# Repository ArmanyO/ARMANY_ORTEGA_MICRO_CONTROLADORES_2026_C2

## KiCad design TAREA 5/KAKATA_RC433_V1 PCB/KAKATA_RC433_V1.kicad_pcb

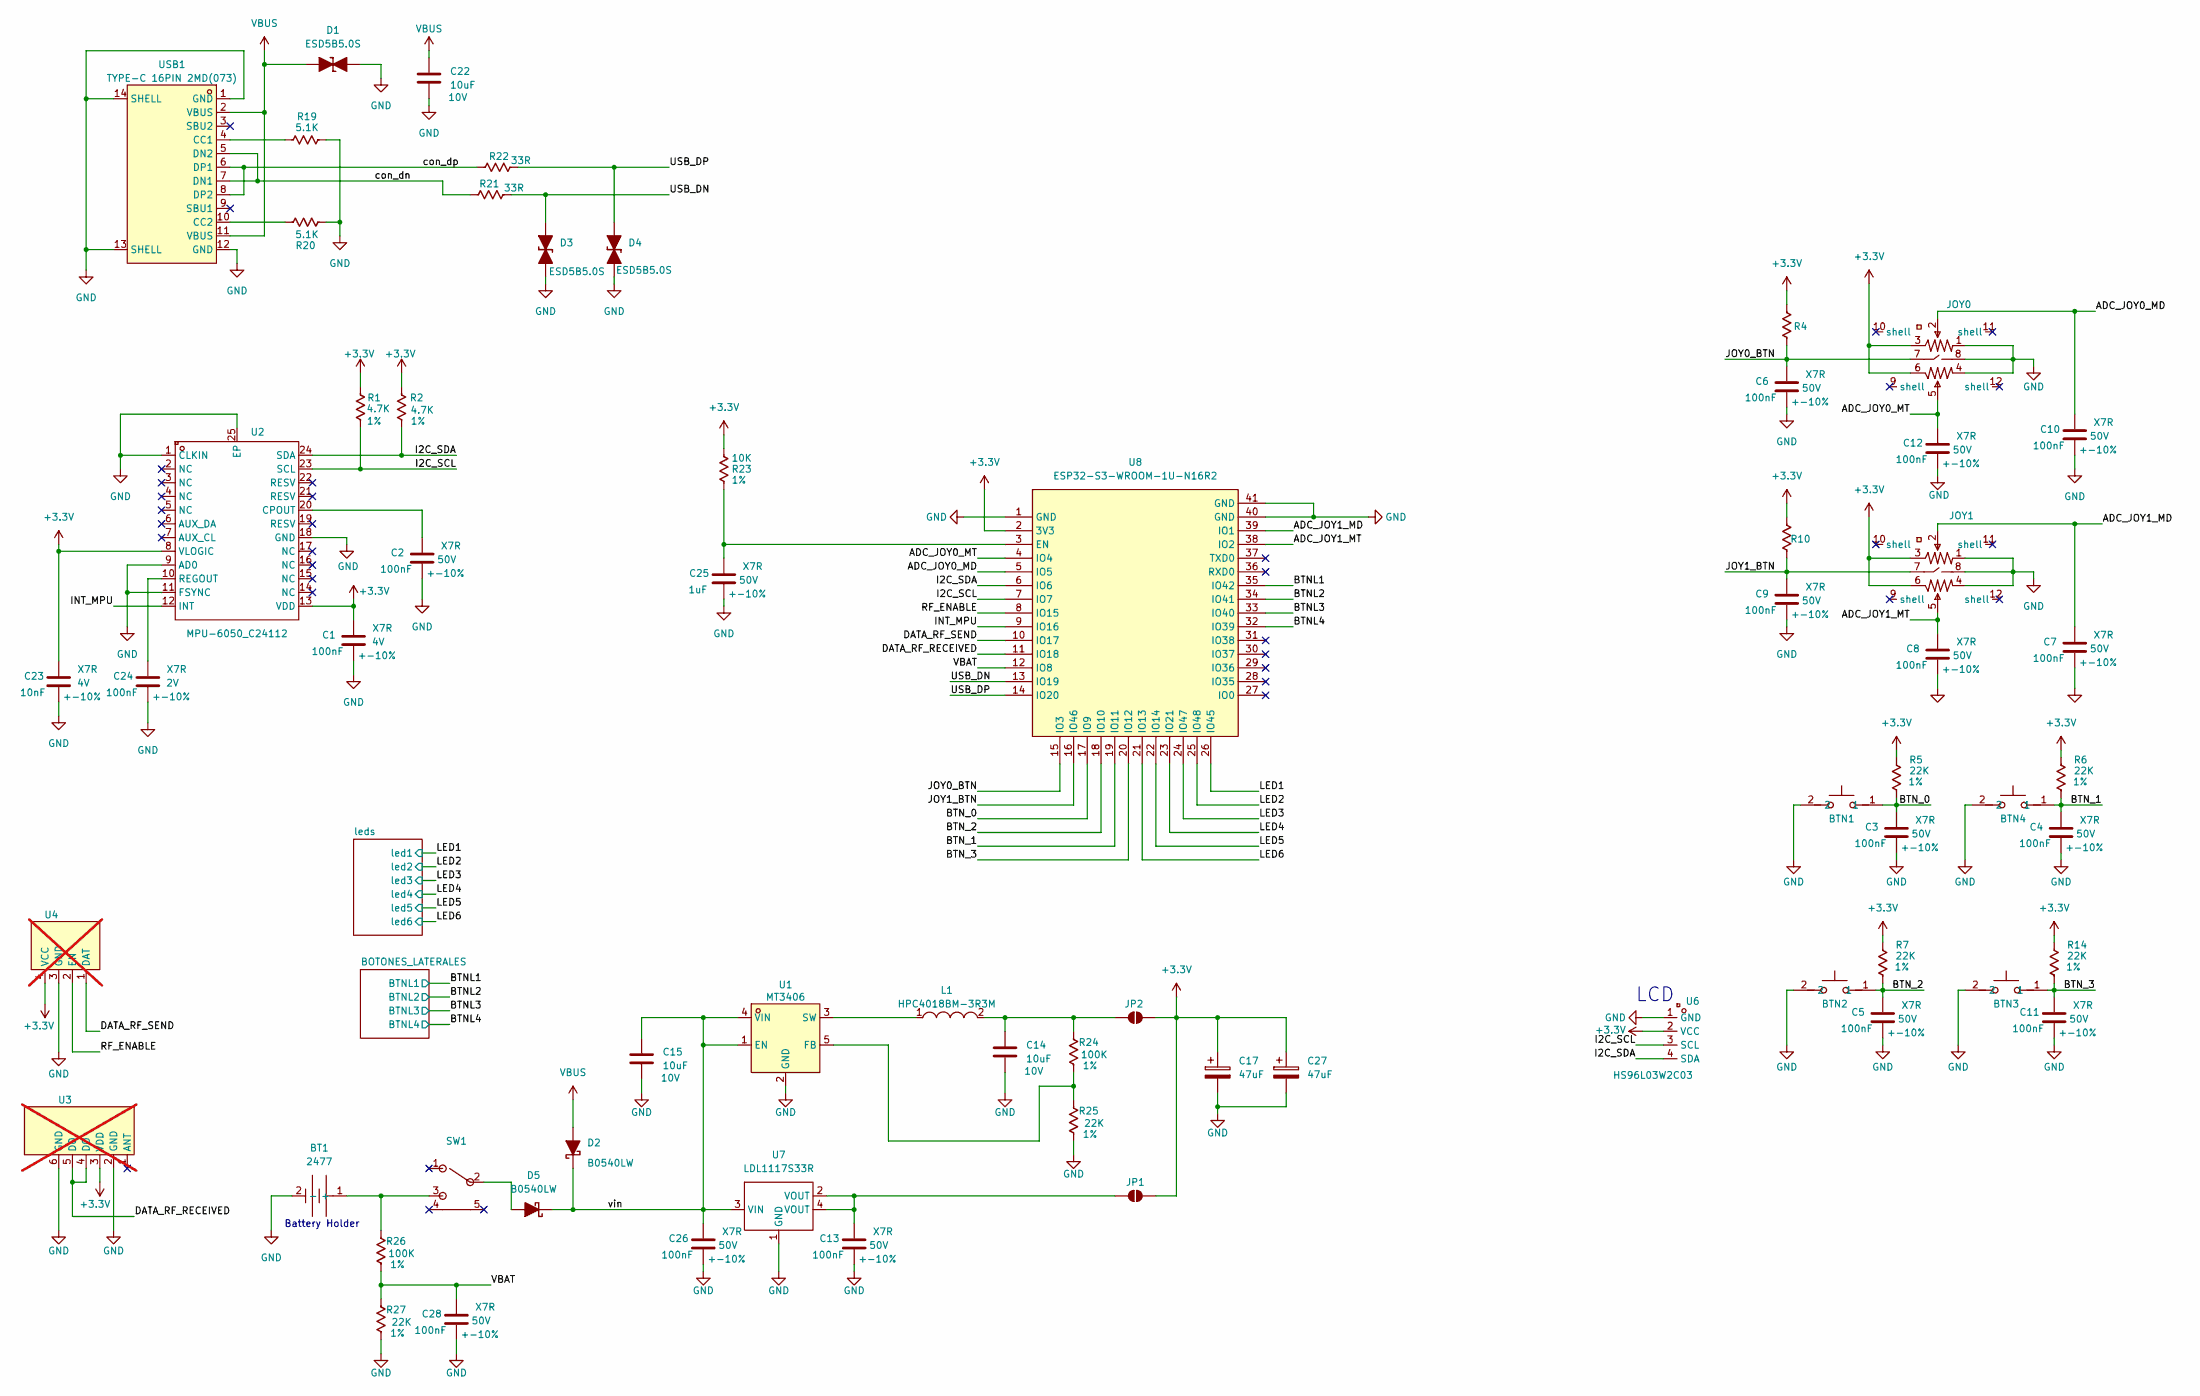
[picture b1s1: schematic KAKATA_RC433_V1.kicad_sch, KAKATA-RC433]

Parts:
BT1: 2477; BAT-TH_2477; LCSC Part C238090
BTN1, BTN2, BTN3, BTN4: CPG151101D01; SW-TH_CPG151101D9X; LCSC Part C49234238
C1, C24: 100nF; C_0603_1608Metric; LCSC Part C519438
C2, C3, C4, C5, C6, C7, C8, C9, C10, C11, C12, C13, C26, C28: 100nF; C_0603_1608Metric; LCSC Part C14663
C14, C15, C22: 10uF; C_0805_2012Metric; LCSC Part # C15850
C17, C27: 47uF; CP_Elec_6.3x5.2; LCSC Part C72522
C23: 10nF; C_0603_1608Metric; LCSC Part C100042
C25: 1uF; C_0603_1608Metric; LCSC Part C559769
D1, D3, D4: ESD5B5.0S; D_SOD-523; LCSC Part # C5172939
D2, D5: B0540LW; D_SOD-123; LCSC Part # C8570
JOY0, JOY1: YF16S-FL7.2-B5KB(45-10)-Y; JOYTICK-TH_YF16S-FL7.2-B5KB-45-10-Y_1; LCSC Part C37323740
JP1, JP2: SolderJumper_2_Open; SolderJumper-2_P1.3mm_Open_RoundedPad1.0x1.5mm
L1: HPC4018BM-3R3M; IND-SMD_L4.0-W4.0_HPC4030NF; PART_NUMBER HPC4018BM-3R3M; LCSC Part C692161
R1, R2: 4.7K; R_0603_1608Metric; LCSC Part C99782
R4, R5, R6, R7, R10, R14, R25, R27: 22K; R_0603_1608Metric; LCSC Part C114065
R19, R20: 5.1K; R_0603_1608Metric; LCSC Part # C105580
R21, R22: 33R; R_0603_1608Metric; LCSC Part # C108661
R23: 10K; R_0603_1608Metric; LCSC Part C98220
R24, R26: 100K; R_0603_1608Metric; LCSC Part C14675
SW1: ST-0-102-C03-N003-RS; SW-TH_ST-0-102-C03-N003-RS; LCSC Part C1788489
U1: MT3406; SOT-23-5_L2.9-W1.6-P0.95-LS2.8-BR; LCSC Part C22462728
U2: MPU-6050_C24112; QFN-24_L4.0-W4.0-P0.50-BL-EP2.7; LCSC Part C24112
U3: 433 MHz RF RECEIVER; rf_433mhz_receiver; not fitted
U4: 433 MHz TRANSMITTER; RF_433MHz_transmisor; not fitted
U6: HS96L03W2C03; OLED-TH_L27.8-W27.2-P2.54_C9900033791; LCSC Part C5248080
U7: LDL1117S33R; SOT-223-4_L6.5-W3.5-P2.30-LS7.0-BR; LCSC Part C435835
U8: ESP32-S3-WROOM-1U-N16R2; WIRELM-SMD_ESP32-S3-WROOM-1U; LCSC Part C3013945
USB1: TYPE-C 16PIN 2MD(073); USB-C-SMD_TYPE-C-6PIN-2MD-073; LCSC Part C2765186

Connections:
+3.3V: C1.1, C17.1, C23.1, C27.1, JOY0.3, JOY0.6, JOY1.3, JOY1.6, JP1.2 (B), JP2.2 (B), R1.1, R2.1, R4.1, R5.2, R6.2, R7.2, R10.1, R14.2, R23.1, U2.8 (VLOGIC), U2.13 (VDD), U3.3 (VDD), U4.4 (VCC), U6.2 (VCC), U8.2 (3V3); also elsewhere on the board
/ADC_JOY0_MD: C10.1, JOY0.2, U8.5 (IO5)
/ADC_JOY0_MT: C12.1, JOY0.5, U8.4 (IO4)
/ADC_JOY1_MD: C7.1, JOY1.2, U8.39 (IO1)
/ADC_JOY1_MT: C8.1, JOY1.5, U8.38 (IO2)
/BTNL1: U8.35 (IO42); also elsewhere on the board
/BTNL2: U8.34 (IO41); also elsewhere on the board
/BTNL3: U8.33 (IO40); also elsewhere on the board
/BTNL4: U8.32 (IO39); also elsewhere on the board
/BTN_0: BTN1.1, C3.1, R5.1, U8.17 (IO9)
/BTN_1: BTN4.1, C4.1, R6.1, U8.19 (IO11)
/BTN_2: BTN2.1, C5.1, R7.1, U8.18 (IO10)
/BTN_3: BTN3.1, C11.1, R14.1, U8.20 (IO12)
/DATA_RF_RECEIVED: U3.4 (DO), U3.5 (DO), U8.11 (IO18)
/DATA_RF_SEND: U4.1 (DAT), U8.10 (IO17)
/I2C_SCL: R1.2, U2.23 (SCL), U6.3 (SCL), U8.7 (IO7)
/I2C_SDA: R2.2, U2.24 (SDA), U6.4 (SDA), U8.6 (IO6)
/INT_MPU: U2.12 (INT), U8.9 (IO16)
/JOY0_BTN: C6.1, JOY0.7, R4.2, U8.15 (IO3)
/JOY1_BTN: C9.1, JOY1.7, R10.2, U8.16 (IO46)
/LED1: U8.26 (IO45); also elsewhere on the board
/LED2: U8.25 (IO48); also elsewhere on the board
/LED3: U8.24 (IO47); also elsewhere on the board
/LED4: U8.23 (IO21); also elsewhere on the board
/LED5: U8.22 (IO14); also elsewhere on the board
/LED6: U8.21 (IO13); also elsewhere on the board
/RF_ENABLE: U4.2 (EN), U8.8 (IO15)
/USB_DN: D3.2 (A), R21.2, U8.13 (IO19)
/USB_DP: D4.2 (A), R22.2, U8.14 (IO20)
/VBAT: C28.1, R26.2, R27.1, U8.12 (IO8)
/con_dn: R21.1, USB1.5 (DN2), USB1.7 (DN1)
/con_dp: R22.1, USB1.6 (DP1), USB1.8 (DP2)
/vin: C15.1, C26.1, D2.1 (K), D5.1 (K), U1.1 (EN), U1.4 (VIN), U7.3 (VIN)
GND: BT1.2 (-), BTN1.2, BTN2.2, BTN3.2, BTN4.2, C1.2, C2.2, C3.2, C4.2, C5.2, C6.2, C7.2, C8.2, C9.2, C10.2, C11.2, C12.2, C13.2, C14.2, C15.2, C17.2, C22.2, C23.2, C24.2, C25.2, C26.2, C27.2, C28.2, D1.1 (K), D3.1 (K), D4.1 (K), JOY0.1, JOY0.4, JOY0.8, JOY1.1, JOY1.4, JOY1.8, R19.2, R20.2, R25.2, R27.2, U1.2 (GND), U2.1 (CLKIN), U2.9 (AD0), U2.11 (FSYNC), U2.18 (GND), U2.25 (EP), U3.2 (GND), U3.6 (GND), U4.3 (GND), U6.1 (GND), U7.1 (GND), U8.1 (GND), U8.40 (GND), U8.41 (GND), USB1.1 (GND), USB1.12 (GND), USB1.13 (SHELL), USB1.14 (SHELL); also elsewhere on the board
unnamed: BT1.1 (+), R26.1, SW1.3
unnamed: D5.2 (A), SW1.2
unnamed: C13.1, JP1.1 (A), U7.2 (VOUT), U7.4 (VOUT)
unnamed: C14.1, JP2.1 (A), L1.2, R24.1
unnamed: R24.2, R25.1, U1.5 (FB)
unnamed: L1.1, U1.3 (SW)
unnamed: C2.1, U2.20 (CPOUT)
unnamed: C24.1, U2.10 (REGOUT)
unnamed: C25.1, R23.2, U8.3 (EN)
unnamed: R19.1, USB1.4 (CC1)
unnamed: R20.1, USB1.10 (CC2)
VBUS: C22.1, D1.2 (A), D2.2 (A), USB1.2 (VBUS), USB1.11 (VBUS)

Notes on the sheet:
Battery Holder
LCD

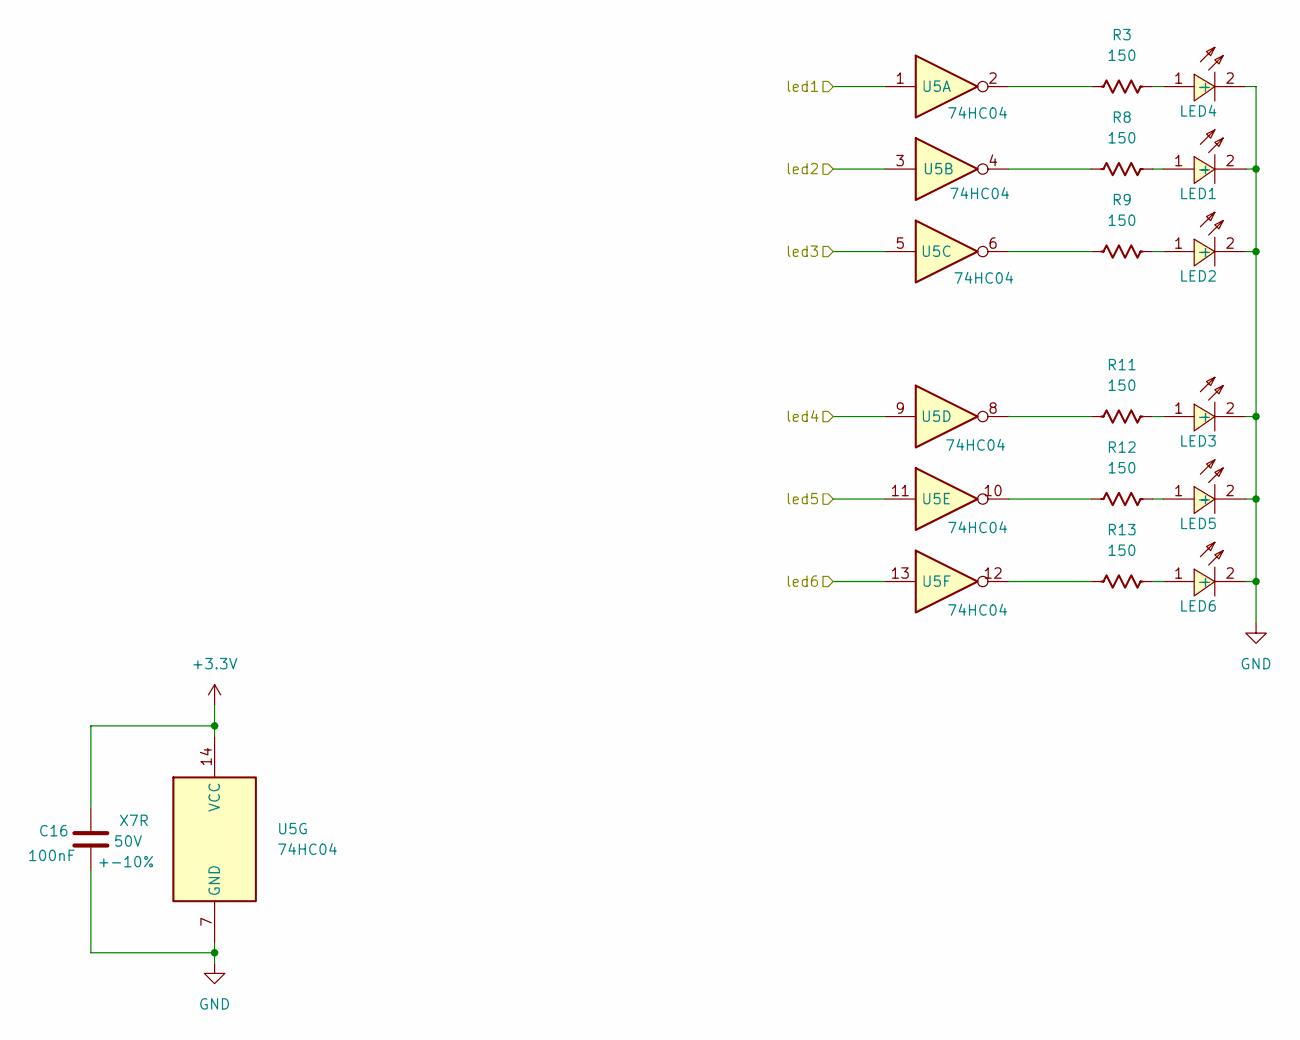
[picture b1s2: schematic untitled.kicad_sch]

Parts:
C16: 100nF; C_0603_1608Metric; LCSC Part C14663
LED1, LED2, LED3, LED4, LED5, LED6: YLED0603R; LED_0603_1608Metric; LCSC Part C19171390
R3, R8, R9, R11, R12, R13: 150; R_0603_1608Metric; LCSC Part C107696
U5: 74HC04; SOIC-14_3.9x8.65mm_Pitch1.27mm; LCSC Part C5590

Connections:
+3.3V: C16.1, U5.14 (VCC); also elsewhere on the board
/LED1: U5.1; also elsewhere on the board
/LED2: U5.3; also elsewhere on the board
/LED3: U5.5; also elsewhere on the board
/LED4: U5.9; also elsewhere on the board
/LED5: U5.11; also elsewhere on the board
/LED6: U5.13; also elsewhere on the board
GND: C16.2, LED1.2 (-), LED2.2 (-), LED3.2 (-), LED4.2 (-), LED5.2 (-), LED6.2 (-), U5.7 (GND); also elsewhere on the board
unnamed: LED1.1 (+), R8.2
unnamed: LED2.1 (+), R9.2
unnamed: LED3.1 (+), R11.2
unnamed: LED4.1 (+), R3.2
unnamed: LED5.1 (+), R12.2
unnamed: LED6.1 (+), R13.2
unnamed: R3.1, U5.2
unnamed: R8.1, U5.4
unnamed: R9.1, U5.6
unnamed: R11.1, U5.8
unnamed: R12.1, U5.10
unnamed: R13.1, U5.12

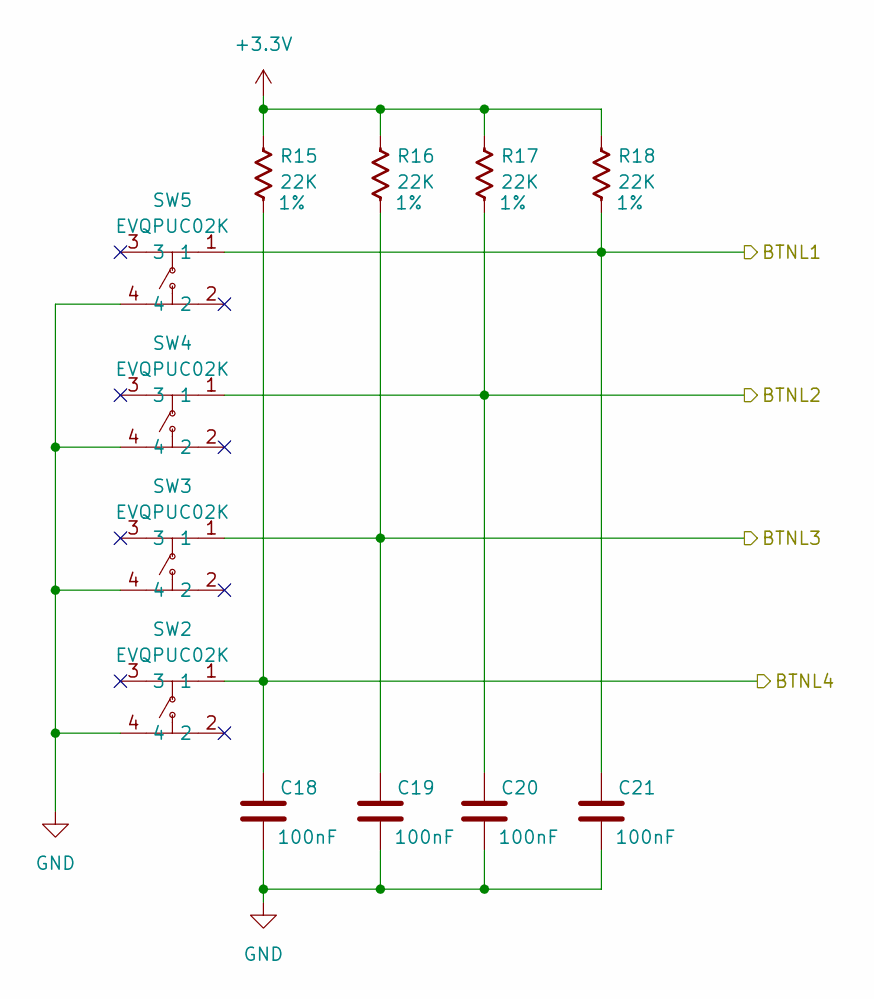
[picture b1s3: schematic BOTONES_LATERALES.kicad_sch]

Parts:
C18, C19, C20, C21: 100nF; C_0603_1608Metric; LCSC Part C14663
R15, R16, R17, R18: 22K; R_0603_1608Metric; LCSC Part C114065
SW2, SW3, SW4, SW5: EVQPUC02K; SW-SMD_EVQPUD02K; LCSC Part C79174

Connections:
+3.3V: R15.1, R16.1, R17.1, R18.1; also elsewhere on the board
/BTNL1: C21.1, R18.2, SW5.1; also elsewhere on the board
/BTNL2: C20.1, R17.2, SW4.1; also elsewhere on the board
/BTNL3: C19.1, R16.2, SW3.1; also elsewhere on the board
/BTNL4: C18.1, R15.2, SW2.1; also elsewhere on the board
GND: C18.2, C19.2, C20.2, C21.2, SW2.4, SW3.4, SW4.4, SW5.4; also elsewhere on the board

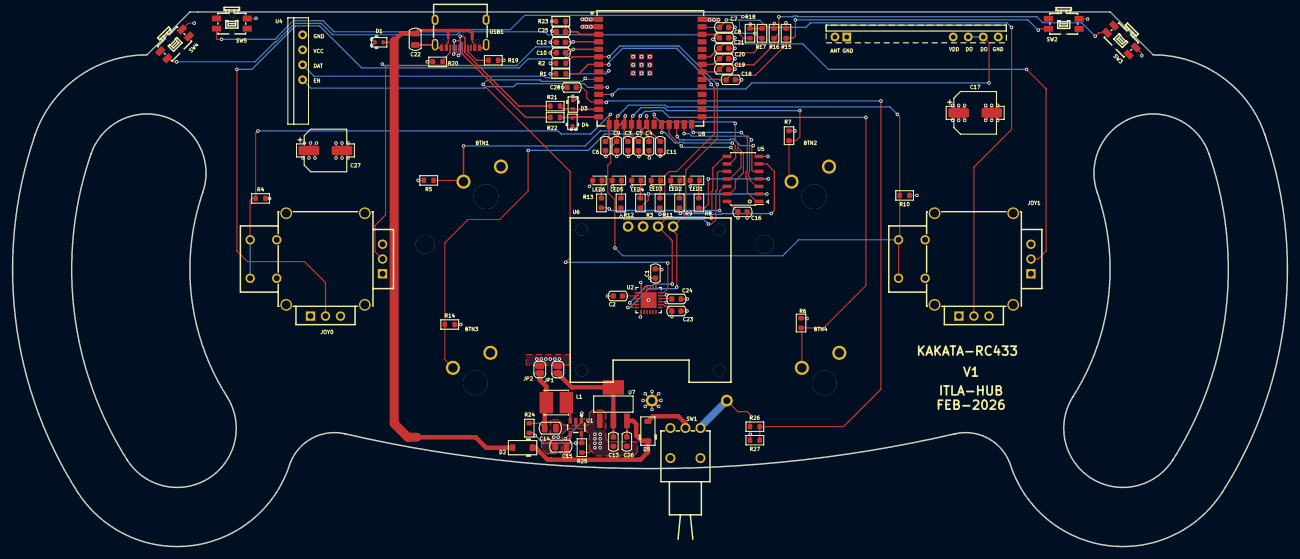
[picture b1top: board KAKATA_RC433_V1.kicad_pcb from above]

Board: 4 copper layers, 215.7 x 90.3 mm, 90 parts (1 on the bottom side), 58 nets.

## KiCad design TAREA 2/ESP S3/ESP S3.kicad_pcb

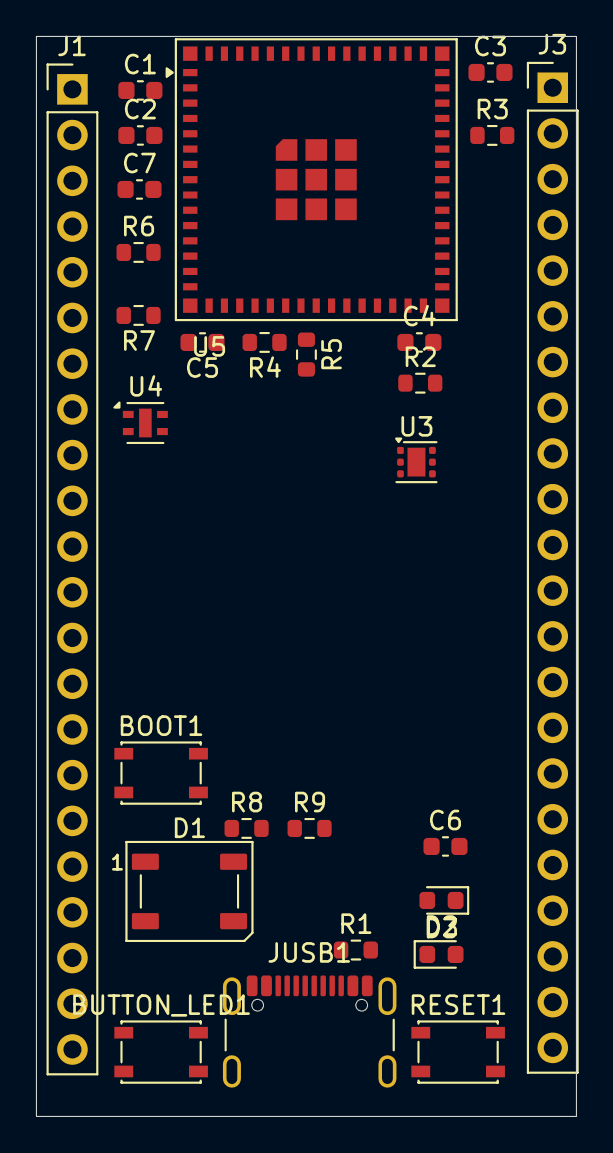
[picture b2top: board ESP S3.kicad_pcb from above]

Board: 2 copper layers, 30.0 x 60.0 mm, 28 parts (0 on the bottom side), 48 nets, no tracks yet.

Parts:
BOOT1: SW_SPST_PTS810
BUTTON_LED1: SW_SPST_PTS810
C1, C3, C4, C5: 0.1uF; C_0603_1608Metric
C2, C6, C7: 10uF; C_0603_1608Metric
D1: WS2812B; LED_WS2812B_PLCC4_5.0x5.0mm_P3.2mm
D2, D3: LED; LED_0603_1608Metric
J1, J3: PinHeader_1x22_P2.54mm_Vertical
JUSB1: USB_C_Receptacle_USB2.0; USB_C_Receptacle_GCT_USB4105-xx-A_16P_TopMnt_Horizontal
R1, R2, R8, R9: 5.1k; R_0603_1608Metric
R3, R4, R5: 10k; R_0603_1608Metric
R6: 1M; R_0603_1608Metric
R7: 200k; R_0603_1608Metric
RESET1: SW_SPST_PTS810
U3: TLV75801PDRV; WSON-6-1EP_2x2mm_P0.65mm_EP1x1.6mm
U4: ENS210; AMS_QFN-4-1EP_2x2mm_P0.95mm_EP0.7x1.6mm
U5: ESP32-S3-MINI-1U; ESP32-S2-MINI-1U

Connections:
/3V3: C1.1, C2.1, C5.1, C7.1, D1.1 (VDD), J1.1, R3.2, R4.2, R5.2, R6.2, R8.1, U3.1 (OUT), U4.1 (VDD), U5.3 (3V3)
/5VUSB: C6.1, J1.21, JUSB1.A4 (VBUS), JUSB1.A9 (VBUS), JUSB1.B4 (VBUS), JUSB1.B9 (VBUS), U3.4 (EN), U3.6 (IN)
/ESP32_EN: C3.1, J3.2, R3.1, U5.45 (EN)
/GPIO0: C4.1, J1.2, U5.4 (IO0)
/GPIO1: J1.3, U5.5 (IO1)
/GPIO2: J1.4, U5.6 (IO2)
/GPIO3: J1.5, U5.7 (IO3)
/GPIO4: J1.6, U5.8 (IO4)
/GPIO5: J1.7, U5.9 (IO5)
/GPIO6: J1.8, U5.10 (IO6)
/GPIO7: J1.9, U5.11 (IO7)
/GPIO8: J1.10, U5.12 (IO8)
/GPIO9: J1.11, U5.13 (IO9)
/GPIO10: J1.12, U5.14 (IO10)
/GPIO11: J1.13, U5.15 (IO11)
/GPIO12: J1.14, U5.16 (IO12)
/GPIO13: J1.15, U5.17 (IO13)
/GPIO14: J1.16, U5.18 (IO14)
/GPIO15: J1.17, U5.19 (IO15)
/GPIO16: J1.18, U5.20 (IO16)
/GPIO21: J3.18, U5.25 (IO21)
/GPIO26: J3.17, U5.26 (IO26)
/GPIO33: J3.16, U5.28 (IO33)
/GPIO34: J3.15, U5.29 (IO34)
/GPIO35: J3.14, U5.31 (IO35)
/GPIO36: J3.13, U5.32 (IO36)
/GPIO37: J3.12, U5.33 (IO37)
/GPIO38: J3.11, U5.34 (IO38)
/GPIO39: J3.10, U5.35 (IO39)
/GPIO40: J3.9, U5.36 (IO40)
/GPIO41: J3.8, U5.37 (IO41)
/GPIO42: J3.7, U5.38 (IO42)
/GPIO45: J3.4, U5.41 (IO45)
/GPIO46: J3.3, U5.44 (IO46)
/GPIO47: J3.22, U5.27 (IO47)
/GPIO48: D1.4 (DIN), J3.21, U5.30 (IO48)
/I2C_SCL: J1.19, R4.1, U4.2 (SCL), U5.21 (IO17)
/I2C_SDA: J1.20, R5.1, U4.3 (SDA), U5.22 (IO18)
/RXD: J3.5, U5.40 (RXD0)
/TXD: J3.6, U5.39 (TXD0)
/USB_N: JUSB1.A7 (D-), JUSB1.B7 (D-), U5.23 (USB_D-)
/USB_P: JUSB1.A6 (D+), JUSB1.B6 (D+), U5.24 (USB_D+)
GND: BOOT1.1, BOOT1.2, C1.2, C2.2, C3.2, C4.2, C5.2, C6.2, C7.2, D1.3 (VSS), D2.1 (K), D3.1 (K), J1.22, J3.1, JUSB1.A1 (GND), JUSB1.A12 (GND), JUSB1.B1 (GND), JUSB1.B12 (GND), R1.2, R2.2, R7.1, RESET1.1, RESET1.2, U3.3 (GND), U3.7 (GND), U4.4 (GND), U4.5 (GND), U5.1 (GND), U5.2 (GND), U5.42 (GND), U5.43 (GND), U5.46 (GND), U5.47 (GND), U5.48 (GND), U5.49 (GND), U5.50 (GND), U5.51 (GND), U5.52 (GND), U5.53 (GND), U5.54 (GND), U5.55 (GND), U5.56 (GND), U5.57 (GND), U5.58 (GND), U5.59 (GND), U5.60 (GND), U5.61 (GND), U5.62 (GND), U5.63 (GND), U5.64 (GND), U5.65 (GND)
unnamed: BUTTON_LED1.1, BUTTON_LED1.2, R9.2
unnamed: D2.2 (A), R8.2, R9.1
unnamed: JUSB1.A5 (CC1), R2.1
unnamed: JUSB1.B5 (CC2), R1.1
unnamed: R6.1, R7.2, U3.2 (FB)

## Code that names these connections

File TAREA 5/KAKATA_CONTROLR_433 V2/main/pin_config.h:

#ifndef PIN_CONFIG_H
#define PIN_CONFIG_H

// ============================================================
// KAKATA RC433 V1 - ESP32-S3 Pin Configuration
// Derived from PCB layout (KAKATA_RC433_V1.kicad_pcb)
// Designer: Carlos Pichardo / ITLA-HUB (2026-02-22)
// ============================================================

// --- I2C Bus (shared: MPU-6050 + OLED) ---
#define PIN_I2C_SDA         6
#define PIN_I2C_SCL         7

// --- Joysticks (Analog X/Y + Digital Button) ---
#define PIN_JOY0_MT         4   // ADC1_CH3 - Joystick 0 top
#define PIN_JOY0_MD         5   // ADC1_CH4 - Joystick 0 middle
#define PIN_JOY1_MT         2   // ADC1_CH1 - Joystick 1 top
#define PIN_JOY1_MD         1   // ADC1_CH0 - Joystick 1 middle
#define PIN_JOY0_BTN        3   // Active-low, external 22k pull-up
#define PIN_JOY1_BTN        46  // Active-low, external 22k pull-up

// --- Arcade Buttons (active-low, 22k pull-up) ---
#define PIN_BTN_0           9
#define PIN_BTN_1           11
#define PIN_BTN_2           10
#define PIN_BTN_3           12

// --- Side Buttons (active-low, 22k pull-up) ---
#define PIN_BTNL1           42
#define PIN_BTNL2           41
#define PIN_BTNL3           40
#define PIN_BTNL4           39

// --- LEDs (driven through 74HC04 inverter, active-low) ---
#define PIN_LED1            45
#define PIN_LED2            48
#define PIN_LED3            47
#define PIN_LED4            21
#define PIN_LED5            14
#define PIN_LED6            13

// --- RF 433 MHz ---
#define PIN_RF_RX           18  // Receiver data output
#define PIN_RF_TX           17  // Transmitter data input
#define PIN_RF_ENABLE       15  // Transmitter enable (active-high)

// --- MPU-6050 ---
#define PIN_MPU_INT         16  // Interrupt output from MPU-6050

// --- Battery ---
#define PIN_VBAT            8   // ADC1_CH0 - Battery voltage divider

// --- USB (HW peripheral, not GPIO) ---
// USB_DN -> IO19 (USB_N)
// USB_DP -> IO20 (USB_P)

#endif // PIN_CONFIG_H

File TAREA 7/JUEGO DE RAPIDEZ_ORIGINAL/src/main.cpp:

#include <Arduino.h>
#include <WiFi.h>
#include <PubSubClient.h>

// ===== CONFIGURACIÓN WIFI =====
const char* ssid = "Las Penas";
const char* password = "Pena123321";

// ===== MQTT BROKER =====
const char* mqtt_server = "broker.emqx.io";
const int mqtt_port = 1883;
const char* mqtt_user = "";
const char* mqtt_pass = "";

// ===== PINES =====
#define BTN1_PIN 4        // GPIO4 = Botón 1 (Active LOW, pull-up)
#define BTN2_PIN 13       // GPIO13 = Botón 2 (Active LOW, pull-up)
#define LED1_PIN 2        // GPIO2 = LED integrado
#define LED2_PIN 15       // GPIO15 = Segundo LED

WiFiClient espClient;
PubSubClient client(espClient);

enum GameState {
  WAITING_START,
  HOLDING_BTN1,
  LED1_ON_WAIT_RELEASE,
  WAIT_BTN2_PRESS,
  SHOW_RESULTS
};

GameState state = WAITING_START;
volatile uint32_t led1_on_time = 0;
volatile uint32_t btn1_release_time = 0;
volatile uint32_t reaction1 = 0;
volatile uint32_t reaction2 = 0;

// Variables Debounce
uint32_t btn1_debounce = 0;
bool btn1_last = false;
bool btn1_stable = false;

uint32_t btn2_debounce = 0;
bool btn2_last = false;
bool btn2_stable = false;

uint32_t hold_start = 0;

// Lectura de hardware
inline bool readBtn1() { return digitalRead(BTN1_PIN) == LOW; } // true si está presionado
inline bool readBtn2() { return digitalRead(BTN2_PIN) == LOW; } // true si está presionado
inline void led1On()   { digitalWrite(LED1_PIN, HIGH); }
inline void led1Off()  { digitalWrite(LED1_PIN, LOW); }
inline void led2On()   { digitalWrite(LED2_PIN, HIGH); }
inline void led2Off()  { digitalWrite(LED2_PIN, LOW); }

void setup_wifi() {
  Serial.print("Conectando a Wi-Fi: ");
  Serial.println(ssid);
  WiFi.begin(ssid, password);
  while (WiFi.status() != WL_CONNECTED) {
    delay(500);
    Serial.print(".");
  }
  Serial.println("\nWi-Fi Conectado!");
}

void reconnect() {
  while (!client.connected()) {
    Serial.print("Intentando conexion MQTT...");
    String clientId = "ESP32-Game-" + String(random(0xffff), HEX);
    if (client.connect(clientId.c_str(), mqtt_user, mqtt_pass)) {
      Serial.println(" Conectado a EMQX!");
      client.subscribe("reaction_game/control");
      client.publish("topic/qos0", "ESP32 listo para jugar");
    } else {
      Serial.print(" Fallo rc=");
      Serial.print(client.state());
      Serial.println(" Reintentando en 2s...");
      delay(2000);
    }
  }
}

void publishTimes() {
  String payload = "{\"reaction1_ms\":" + String(reaction1) + ",\"reaction2_ms\":" + String(reaction2) + "}";
  client.publish("reaction_game/times", payload.c_str());
  
  String msg = "Reaccion 1: " + String(reaction1) + " ms | Reaccion 2: " + String(reaction2) + " ms";
  client.publish("topic/qos0", msg.c_str());
  Serial.println("-> Datos publicados en MQTT!");
}

void setup() {
  Serial.begin(115200);
  delay(1000); // Tiempo para estabilizar el Monitor Serie
  Serial.println("\n--- Iniciando ESP32 ---");

  pinMode(BTN1_PIN, INPUT_PULLUP);
  pinMode(BTN2_PIN, INPUT_PULLUP);
  pinMode(LED1_PIN, OUTPUT);
  pinMode(LED2_PIN, OUTPUT);
  led1Off(); 
  led2Off();

  // Red y Semilla aleatoria usando hardware del ESP32
  setup_wifi();
  randomSeed(esp_random()); 
  client.setServer(mqtt_server, mqtt_port);
}

void loop() {
  if (!client.connected()) reconnect();
  client.loop();

  uint32_t now = micros();

  // Debounce Botón 1 (BOOT)
  bool btn1_raw = readBtn1();
  if (btn1_raw != btn1_last) { 
    btn1_debounce = now; 
    btn1_last = btn1_raw; 
  }
  if (now - btn1_debounce > 2000) { 
    btn1_stable = btn1_raw;
  }

  // Debounce Botón 2
  bool btn2_raw = readBtn2();
  if (btn2_raw != btn2_last) { 
    btn2_debounce = now; 
    btn2_last = btn2_raw; 
  }
  if (now - btn2_debounce > 2000) { 
    btn2_stable = btn2_raw;
  }

  // Detección de flancos
  static bool btn1_prev = false;
  bool btn1_pressed = btn1_stable;
  bool btn1_fell    = btn1_pressed && !btn1_prev;  
  bool btn1_rose    = !btn1_pressed && btn1_prev;  
  btn1_prev = btn1_pressed;

  static bool btn2_prev = false;
  bool btn2_pressed = btn2_stable;
  bool btn2_fell    = btn2_pressed && !btn2_prev; 
  bool btn2_rose    = !btn2_pressed && btn2_prev;
  btn2_prev = btn2_pressed;

  // Máquina de Estados
  switch (state) {
    case WAITING_START:
      led1Off(); 
      led2Off();
      hold_start = 0;
      if (btn1_fell) {
        Serial.println("-> Boton 1 PRESIONADO. Esperando tiempo aleatorio...");
        state = HOLDING_BTN1;
      }
      break;

    case HOLDING_BTN1:
      if (btn1_rose) { 
        Serial.println("-> Boton 1 soltado muy rapido. Reiniciando...");
        hold_start = 0;
        state = WAITING_START; 
        break; 
      }
      
      if (hold_start == 0) hold_start = now;
      
      if (now - hold_start > (random(1500000, 4500000))) {
        led1On();
        led1_on_time = now;
        Serial.println("-> LED 1 ENCENDIDO! Suelta el Boton 1!");
        state = LED1_ON_WAIT_RELEASE;
        hold_start = 0;
      }
      break;

    case LED1_ON_WAIT_RELEASE:
      if (btn1_rose) {
        btn1_release_time = now;
        reaction1 = (btn1_release_time - led1_on_time) / 1000;
        Serial.printf("-> Reaccion 1: %d ms. Presiona Boton 2 (GPIO12)...\n", reaction1);
        led1Off();
        state = WAIT_BTN2_PRESS;
      }
      break;

    case WAIT_BTN2_PRESS:
      if (btn2_fell) {
        uint32_t btn2_time = now;
        reaction2 = (btn2_time - btn1_release_time) / 1000;
        Serial.printf("-> Reaccion 2: %d ms.\n", reaction2);
        led2On();
        state = SHOW_RESULTS;
      }
      break;

    case SHOW_RESULTS:
      publishTimes();
      delay(2000);
      led2Off();
      state = WAITING_START;
      break;
  }
}

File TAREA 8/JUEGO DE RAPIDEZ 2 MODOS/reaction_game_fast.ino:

#include <ESP8266WiFi.h>
#include <PubSubClient.h>

const char* ssid = "Rapidito";
const char* password = "Adm1N2584km";
const char* mqtt_server = "mqtt://broker.emqx.io";
const int mqtt_port = 1883;
const char* mqtt_user = "USUARIO_MQTT";
const char* mqtt_pass = "PASSWORD_MQTT";

#define BTN1_PIN 5   // D1 = GPIO5
#define BTN2_PIN 4   // D2 = GPIO4
#define LED1_PIN 14  // D5 = GPIO14
#define LED2_PIN 12  // D6 = GPIO12

WiFiClient espClient;
PubSubClient client(espClient);

enum GameState {
  WAITING_START,
  HOLDING_BTN1,
  LED1_ON_WAIT_RELEASE,
  WAIT_BTN2_PRESS,
  SHOW_RESULTS
};

GameState state = WAITING_START;
volatile uint32_t led1_on_time = 0;
volatile uint32_t btn1_release_time = 0;
volatile uint32_t reaction1 = 0;
volatile uint32_t reaction2 = 0;

uint32_t btn1_debounce = 0;
uint32_t btn2_debounce = 0;
bool btn1_last = true;
bool btn2_last = true;
bool btn1_stable = true;
bool btn2_stable = true;

inline bool readBtn1() { return (GPI & (1 << BTN1_PIN)) == 0; }
inline bool readBtn2() { return (GPI & (1 << BTN2_PIN)) == 0; }
inline void led1On()   { GPOS = (1 << LED1_PIN); }
inline void led1Off()  { GPOC = (1 << LED1_PIN); }
inline void led2On()   { GPOS = (1 << LED2_PIN); }
inline void led2Off()  { GPOC = (1 << LED2_PIN); }

void setup_wifi() {
  WiFi.begin(ssid, password);
  while (WiFi.status() != WL_CONNECTED) delay(500);
}

void reconnect() {
  while (!client.connected()) {
    String clientId = "ESP8266-Game-" + String(random(0xffff), HEX);
    if (client.connect(clientId.c_str(), mqtt_user, mqtt_pass)) {
      client.subscribe("reaction_game/control");
    } else {
      delay(5000);
    }
  }
}

void publishTimes() {
  String payload = "{\"reaction1_ms\":" + String(reaction1) + ",\"reaction2_ms\":" + String(reaction2) + "}";
  client.publish("reaction_game/times", payload.c_str());
}

void setup() {
  pinMode(BTN1_PIN, INPUT_PULLUP);
  pinMode(BTN2_PIN, INPUT_PULLUP);
  pinMode(LED1_PIN, OUTPUT);
  pinMode(LED2_PIN, OUTPUT);
  led1Off(); led2Off();

  Serial.begin(115200);
  setup_wifi();
  client.setServer(mqtt_server, mqtt_port);
  randomSeed(analogRead(A0));
}

void loop() {
  if (!client.connected()) reconnect();
  client.loop();

  uint32_t now = micros();
  bool btn1_raw = readBtn1();
  bool btn2_raw = readBtn2();

  if (btn1_raw != btn1_last) { btn1_debounce = now; btn1_last = btn1_raw; }
  if (btn2_raw != btn2_last) { btn2_debounce = now; btn2_last = btn2_raw; }

  if (now - btn1_debounce > 2000) btn1_stable = btn1_raw;  // 2ms debounce
  if (now - btn2_debounce > 2000) btn2_stable = btn2_raw;

  static bool btn1_prev = true, btn2_prev = true;
  bool btn1_pressed = !btn1_stable;
  bool btn2_pressed = !btn2_stable;
  bool btn1_fell  = btn1_prev && !btn1_pressed;
  bool btn1_rose  = !btn1_prev && btn1_pressed;
  bool btn2_fell  = btn2_prev && !btn2_pressed;
  btn1_prev = btn1_pressed;
  btn2_prev = btn2_pressed;

  switch (state) {
    case WAITING_START:
      led1Off(); led2Off();
      if (btn1_fell) state = HOLDING_BTN1;
      break;

    case HOLDING_BTN1:
      if (btn1_rose) { state = WAITING_START; break; }
      static uint32_t hold_start = 0;
      if (hold_start == 0) hold_start = now;
      if (now - hold_start > (random(1000000, 8000000))) {
        led1On();
        led1_on_time = now;
        state = LED1_ON_WAIT_RELEASE;
        hold_start = 0;
      }
      break;

    case LED1_ON_WAIT_RELEASE:
      if (btn1_rose) {
        reaction1 = (now - led1_on_time) / 1000;
        btn1_release_time = now;
        led1Off();
        state = WAIT_BTN2_PRESS;
      }
      break;

    case WAIT_BTN2_PRESS:
      if (btn2_fell) {
        reaction2 = (now - btn1_release_time) / 1000;
        led2On();
        state = SHOW_RESULTS;
      }
      break;

    case SHOW_RESULTS:
      publishTimes();
      delay(2000);
      led2Off();
      state = WAITING_START;
      break;
  }
}
